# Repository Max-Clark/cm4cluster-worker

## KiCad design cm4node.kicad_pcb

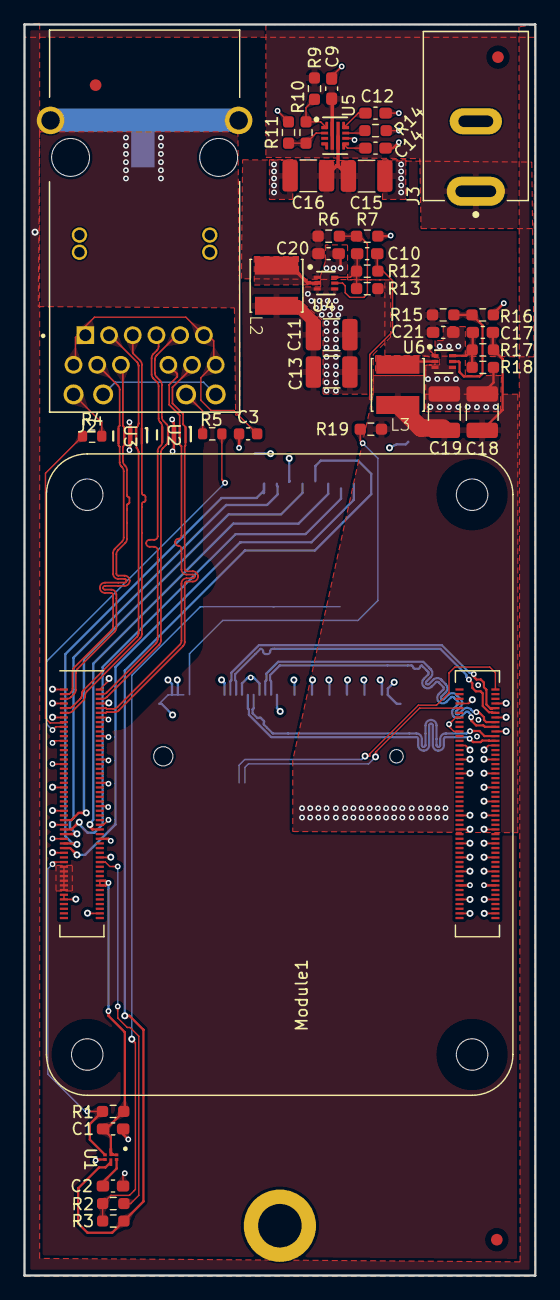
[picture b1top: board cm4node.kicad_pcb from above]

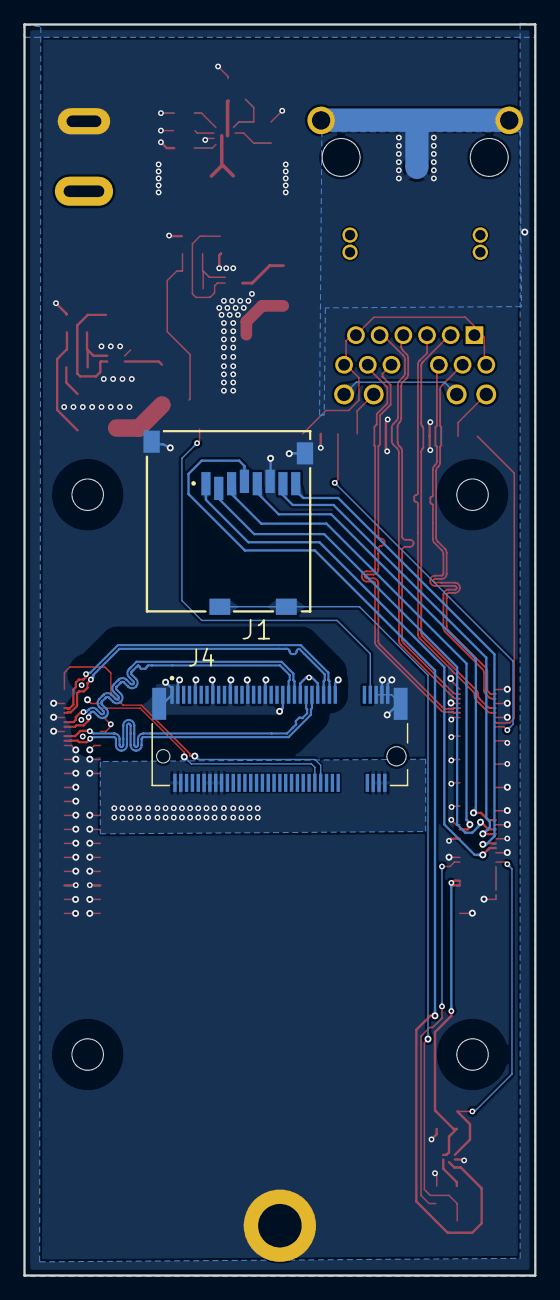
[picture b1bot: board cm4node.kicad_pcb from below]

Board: 4 copper layers, 43.8 x 107.3 mm, 52 parts (3 on the bottom side), 51 nets.

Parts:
C1, C9, C20, C21: 0.1u; C_0603_1608Metric_Pad1.08x0.95mm_HandSolder
C2: DNS; C_0603_1608Metric_Pad1.08x0.95mm_HandSolder
C3: 0.1u; C_0603_1608Metric
C10: 33p; C_0603_1608Metric_Pad1.08x0.95mm_HandSolder
C11, C13, C15, C16, C18, C19: 22u; C_1210_3225Metric_Pad1.33x2.70mm_HandSolder
C12, C14: 2.7n; C_0603_1608Metric_Pad1.08x0.95mm_HandSolder
C17: 56p; C_0603_1608Metric_Pad1.08x0.95mm_HandSolder
D1: cm4lite
FID1, FID2, FID3: Fiducial; Fiducial_1mm_Mask2mm
J1: MEM2061-01-188-00-A_REVA; GCT_MEM2061-01-188-00-A_REVA
J2: 0826-1X1T-M1-F; BEL_0826-1X1T-M1-F
J3: PJ-037AH; CUI_PJ-037AH
J4: 1-2199230-6; TE_1-2199230-6
L2, L3: 1.5u; L_TYA4020
Module1: ComputeModule4-CM4; Raspberry-Pi-4-Compute-Module
NT1: NetTie_2; NetTie-2_SMD_Pad2.0mm
R1: 12k; R_0603_1608Metric_Pad0.98x0.95mm_HandSolder
R2: 0; R_0603_1608Metric_Pad0.98x0.95mm_HandSolder
R3, R6, R15: 100k; R_0603_1608Metric_Pad0.98x0.95mm_HandSolder
R4, R5: 1k; R_0603_1608Metric
R7, R16: 17.4k; R_0603_1608Metric_Pad0.98x0.95mm_HandSolder
R9: 470k; R_0603_1608Metric_Pad0.98x0.95mm_HandSolder
R10: 34.8k; R_0603_1608Metric_Pad0.98x0.95mm_HandSolder
R11: 38.3k; R_0603_1608Metric_Pad0.98x0.95mm_HandSolder
R12: 220k; R_0603_1608Metric_Pad0.98x0.95mm_HandSolder
R13, R18: 30k; R_0603_1608Metric_Pad0.98x0.95mm_HandSolder
R14: 1.54k; R_0603_1608Metric_Pad0.98x0.95mm_HandSolder
R17: 135k; R_0603_1608Metric_Pad0.98x0.95mm_HandSolder
R19: 10k; R_0603_1608Metric_Pad0.98x0.95mm_HandSolder
U1: TPS22995RZFR; WQFN6_RZF_TEX
U2, U3: TPD4E02B04QDQARQ1; DQA0010A
U4, U6: TPS564247DRLR; TPS564242DRLR_TEX
U5: TPS259470ARPWR; RPW0010A-MFG

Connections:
+3.3V: C1.1, J2.18, J2.20, Module1.84 (+3.3v_(Output)), Module1.86 (+3.3v_(Output)), R1.1, U1.1 (VBIAS), U1.2 (VIN)
+3.3V_PCIE: C17.1, C18.1, C19.1, J4.2 (3.3V), J4.4 (3.3V), J4.12 (3.3V), J4.14 (3.3V), J4.16 (3.3V), J4.18 (3.3V), J4.70 (3.3V), J4.72 (3.3V), J4.74 (3.3V), L3.2, R17.1, R19.1
+3.3V_SD: J1.4 (VDD), R3.1, U1.5 (VOUT)
+5V: C10.1, C11.1, C13.1, L2.2, Module1.77 (+5v_(Input)), Module1.79 (+5v_(Input)), Module1.81 (+5v_(Input)), Module1.83 (+5v_(Input)), Module1.85 (+5v_(Input)), Module1.87 (+5v_(Input)), R12.1
+12P: C9.1, J3.1, R9.1, U5.5 (IN)
+12V: C15.1, C16.1, C20.1, C21.1, R6.1, R15.1, U4.1 (VIN), U5.6 (OUT), U6.1 (VIN)
/Ethernet & SD/ETH_0N: J2.10 (TRD1-), Module1.10 (Ethernet_Pair0_N), U2.2 (IO2)
/Ethernet & SD/ETH_0P: J2.11 (TRD1+), Module1.12 (Ethernet_Pair0_P), U2.1 (IO1)
/Ethernet & SD/ETH_1N: J2.5 (TRD2-), Module1.6 (Ethernet_Pair1_N), U2.4 (IO3)
/Ethernet & SD/ETH_1P: J2.4 (TRD2+), Module1.4 (Ethernet_Pair1_P), U2.5 (IO4)
/Ethernet & SD/ETH_2N: J2.2 (TRD3-), Module1.9 (Ethernet_Pair2_N), U3.2 (IO2)
/Ethernet & SD/ETH_2P: J2.3 (TRD3+), Module1.11 (Ethernet_Pair2_P), U3.1 (IO1)
/Ethernet & SD/ETH_3N: J2.9 (TRD4-), Module1.5 (Ethernet_Pair3_N), U3.4 (IO3)
/Ethernet & SD/ETH_3P: J2.8 (TRD4+), Module1.3 (Ethernet_Pair3_P), U3.5 (IO4)
/Ethernet & SD/ETH_LED_G: Module1.17 (Ethernet_nLED2(3.3v)), R5.1
/Ethernet & SD/ETH_LED_Y: Module1.15 (Ethernet_nLED3(3.3v)), R4.1
/Ethernet & SD/Reserved: Module1.76 (Reserved), R2.1
/Ethernet & SD/SD_CLK: J1.5 (CLK), Module1.57 (SD_CLK)
/Ethernet & SD/SD_CMD: J1.3 (CMD), Module1.62 (SD_CMD)
/Ethernet & SD/SD_DAT0: J1.7 (DAT0), Module1.63 (SD_DAT0)
/Ethernet & SD/SD_DAT1: J1.8 (DAT1), Module1.67 (SD_DAT1)
/Ethernet & SD/SD_DAT2: J1.1 (DAT2), Module1.69 (SD_DAT2)
/Ethernet & SD/SD_DAT3: J1.2 (CD/DAT3), Module1.61 (SD_DAT3)
/Ethernet & SD/SD_PWR_ON: Module1.75 (SD_PWR_ON), R1.2, U1.3 (ON)
/USB & PCIe/PCIE_CLK_N: J4.53 (REFCLKN), Module1.112 (PCIe_CLK_N)
/USB & PCIe/PCIE_CLK_P: J4.55 (REFCLKP), Module1.110 (PCIe_CLK_P)
/USB & PCIe/PCIE_CLK_nREQ: J4.52 (CLKREQ#), Module1.102 (PCIe_CLK_nREQ)
/USB & PCIe/PCIE_RX_N: J4.41 (SATA-B+/PERn0), Module1.118 (PCIe_RX_N)
/USB & PCIe/PCIE_RX_P: J4.43 (SATA-B-/PERp0), Module1.116 (PCIe_RX_P)
/USB & PCIe/PCIE_TX_N: J4.49 (SATA-A+/PETp0), Module1.124 (PCIe_TX_N)
/USB & PCIe/PCIE_TX_P: J4.47 (SATA-A-/PETn0), Module1.122 (PCIe_TX_P)
/USB & PCIe/PCIE_nRST: J4.50 (PERST#), Module1.109 (PCIe_nRST)
GND: C1.2, C2.2, C3.1, C9.2, C11.2, C12.2, C13.2, C14.2, C15.2, C16.2, C18.2, C19.2, C20.2, C21.2, J1.6 (VSS), J1.11 (GND), J1.12 (GND__1), J3.2, J4.1 (CONFIG_3), J4.3 (GND), J4.9 (GND), J4.15 (GND), J4.21 (CONFIG_0), J4.27 (GND), J4.33 (GND), J4.39 (GND), J4.45 (GND), J4.51 (GND), J4.57 (GND), J4.71 (GND), J4.73 (GND), J4.75 (CONFIG_2), J4.GND (CardGND), J4.S1 (SHIELD), J4.S2 (SHIELD__1), Module1.1 (GND), Module1.2 (GND), Module1.7 (GND), Module1.8 (GND), Module1.13 (GND), Module1.14 (GND), Module1.22 (GND), Module1.23 (GND), Module1.32 (GND), Module1.33 (GND), Module1.42 (GND), Module1.43 (GND), Module1.52 (GND), Module1.53 (GND), Module1.59 (GND), Module1.60 (GND), Module1.65 (GND), Module1.66 (GND), Module1.71 (GND), Module1.74 (GND), Module1.89 (WiFi_nDisable), Module1.91 (BT_nDisable), Module1.98 (GND), Module1.107 (GND), Module1.108 (GND), Module1.113 (GND), Module1.114 (GND), Module1.119 (GND), Module1.120 (GND), Module1.125 (GND), Module1.126 (GND), Module1.131 (GND), Module1.132 (GND), Module1.137 (GND), Module1.138 (GND), Module1.144 (GND), Module1.150 (GND), Module1.155 (GND), Module1.156 (GND), Module1.161 (GND), Module1.162 (GND), Module1.167 (GND), Module1.168 (GND), Module1.173 (GND), Module1.174 (GND), Module1.179 (GND), Module1.180 (GND), Module1.185 (GND), Module1.186 (GND), Module1.191 (GND), Module1.192 (GND), Module1.197 (GND), Module1.198 (GND), NT1.1, R7.2, R11.2, R13.2, R14.2, R16.2, R18.2, U1.4 (GND), U2.3 (GND), U3.3 (GND), U4.3 (GND), U4.4 (AGND), U5.8 (GND), U6.3 (GND), U6.4 (AGND)
GNDPWR: J2.S1 (SHIELD), J2.S2 (SHIELD__1), NT1.2
unnamed: J1.9 (CD1), J1.10 (CD2), R2.2, R3.2
unnamed: J2.17, R4.2
unnamed: J2.19, R5.2
unnamed: C3.2, J2.1 (TRCT3), J2.6 (TRCT2), J2.7 (TRCT4), J2.12 (TRCT1)
unnamed: J4.69 (CONFIG_1), R19.2
unnamed: C2.1, U1.6 (CT)
unnamed: R6.2, R7.1, U4.5 (EN)
unnamed: C10.2, R12.2, R13.1, U4.6 (FB)
unnamed: L2.1, U4.2 (SW)
unnamed: R9.2, R10.1, U5.1 (EN_UVLO)
unnamed: R14.1, U5.9 (ILM)
unnamed: C12.1, U5.10 (ITIMER)
unnamed: R10.2, R11.1, U5.2 (OVLO)
unnamed: C14.1, U5.7 (dVdt)
unnamed: R15.2, R16.1, U6.5 (EN)
unnamed: C17.2, R17.2, R18.1, U6.6 (FB)
unnamed: L3.1, U6.2 (SW)

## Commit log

2024-02-21 feat: schematic and layout roughed out
